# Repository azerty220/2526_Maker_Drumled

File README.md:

# 2526_Maker_Drumled

## Elise Firmin

### Description :
 
Le projet consiste à mettre des leds sur la caisse-claire d’une batterie. Ces led s’allumeraient lorsque la caisse-claire reçoit un coup. De plus, il y aurait un encodeur permettant de choisir la couleur de l’éclairage.
Le projet a pour but d’être amovible ; c’est-à-dire qu’il puisse être ajouté puis retiré de la caisse claire. 
Une partie conception 3D est envisagée afin de mettre le projet sur le contour de la caisse claire sans gêner les frappes du batteur, et qu’il n’y ait pas besoin de démonter les peaux pour insérer les leds. Ainsi, nous évitons de faire des trous dans une caisse claire afin de relier l’encodeur.

### Quelques images d'une caisse claire et de ce que l'on trouve actuellement sur le marché :

#### Exemple de caisse claire :
Nous pouvons voir le fût sur lequel l'on pourra fixer le système et le déclencheur que l'on ne doit pas gêner en revanche. 

#### Système d'éclairage existant :

#####

#####

### Rétroplanning du projet :

Se référer à la partie "Projects" avec le nom "Retroplanning".

## Mécanique :

Il a fallu faire attention que le timbre puisse s'enclencher et se déclencher sans problème. Aussi, ne pas supperposer la partie mécanique aux pièces mécaniques de la caisse-claire elle-même. L'imprimante 3D a été choisie de façon à qu'elle ait un plateau suffisamment grand pour imprimer cette pièce mécanique. 

La partie mécanique se fait en 3 parties :

- 2 parties pour l'anneau autour de la caisse claire, qui s'aimante afin que le tout tienne autour de la caisse-claire. Les aimants sont choisis assez puissants (12kg minimum conseillé), et le tout est assez solide pour ne pas glisser vers le bas. L'une des moitiés d'anneau est adaptée pour recevoir le pcb qui se fixe à l'aide de vis et d'un fer à souder chaud. 

- Le support de la batterie, qui possède 4 trous afin de pouvoir le fixer à l'anneau autour de la caisse claire, à l'aide de vis et d'un fer à soudé chaud.

## Le code :

Le seuil du capteur est à régler dans le code du projet. Le code est séparé en plusieurs parties avec notamment les fonctions importantes qui sont exécutées dans la boucle du main. Un fichier concerne l'acquisition du capteur, un autre les données envoyées à la bande neopixel selon la couleur dirigée par le bouton hardware, et l'acquisition du capteur. 

## La batterie :

Malheureusement, la batterie construite ne permet pas de gérer les appels de courants du circuit, en revanche, en branche une alimentation électrique, le projet est fonctionnel. Il faut changer le composant qui permet de rguler les batteries qui sont en série pour en prendre un plus performant, ou bien utiliser une batterie qui possède une seule cellule est une autre soluton. 

## Le hardware

Plusieurs connectiques de composants ont été adaptées pour avoir des connectiques plus petites et réduire la taille du pcb. Notamment la connectique du ruban de led neopixels pour la convertir en un connecteur jmc de petite taille. 

De plus, lors des tests du projet, le maintien du bouton reset était nécessaire pour la compilatiion du code ; ainsi, la résistance R3 du pcb est inutile : elle s'enlève très facilement du pcb à l'aide d'un coupe-ongle par exemple. Ou bien, sans fer à souder, la température d'un briquet étant de 800°C à 1000°C, cela peut être tenté ; mais attention au risque de brûlure. 

La petite taille du pcb permet un poids léger. 

Le PCB a été conçu à l'aide du logiciel KiCad.

## Piste d'amélioration du projet :

Le projet pourrait être amélioré grâce à des effets codés comme un chazer par exmple, puis un bouton hardware associé. 
De plus, il pourrait être pertinent de mettre un bouton qui permettrait en appuyant 4 fois dessus par l'utilisateur de déterminer un BPM et que les led ne s'allument plus à chaque coup cette fois ci, mais à chaque temps, ce qui constiturait une aide pour le batteur pour conserver le tempo.
En mêlant cette dernière idée avec le projet initial, et étendu à la batterie tout entière, cela donnerait l'accès à des personnes mal entendante à cet instrument, que ce soit une sourdité partiel ou complète.

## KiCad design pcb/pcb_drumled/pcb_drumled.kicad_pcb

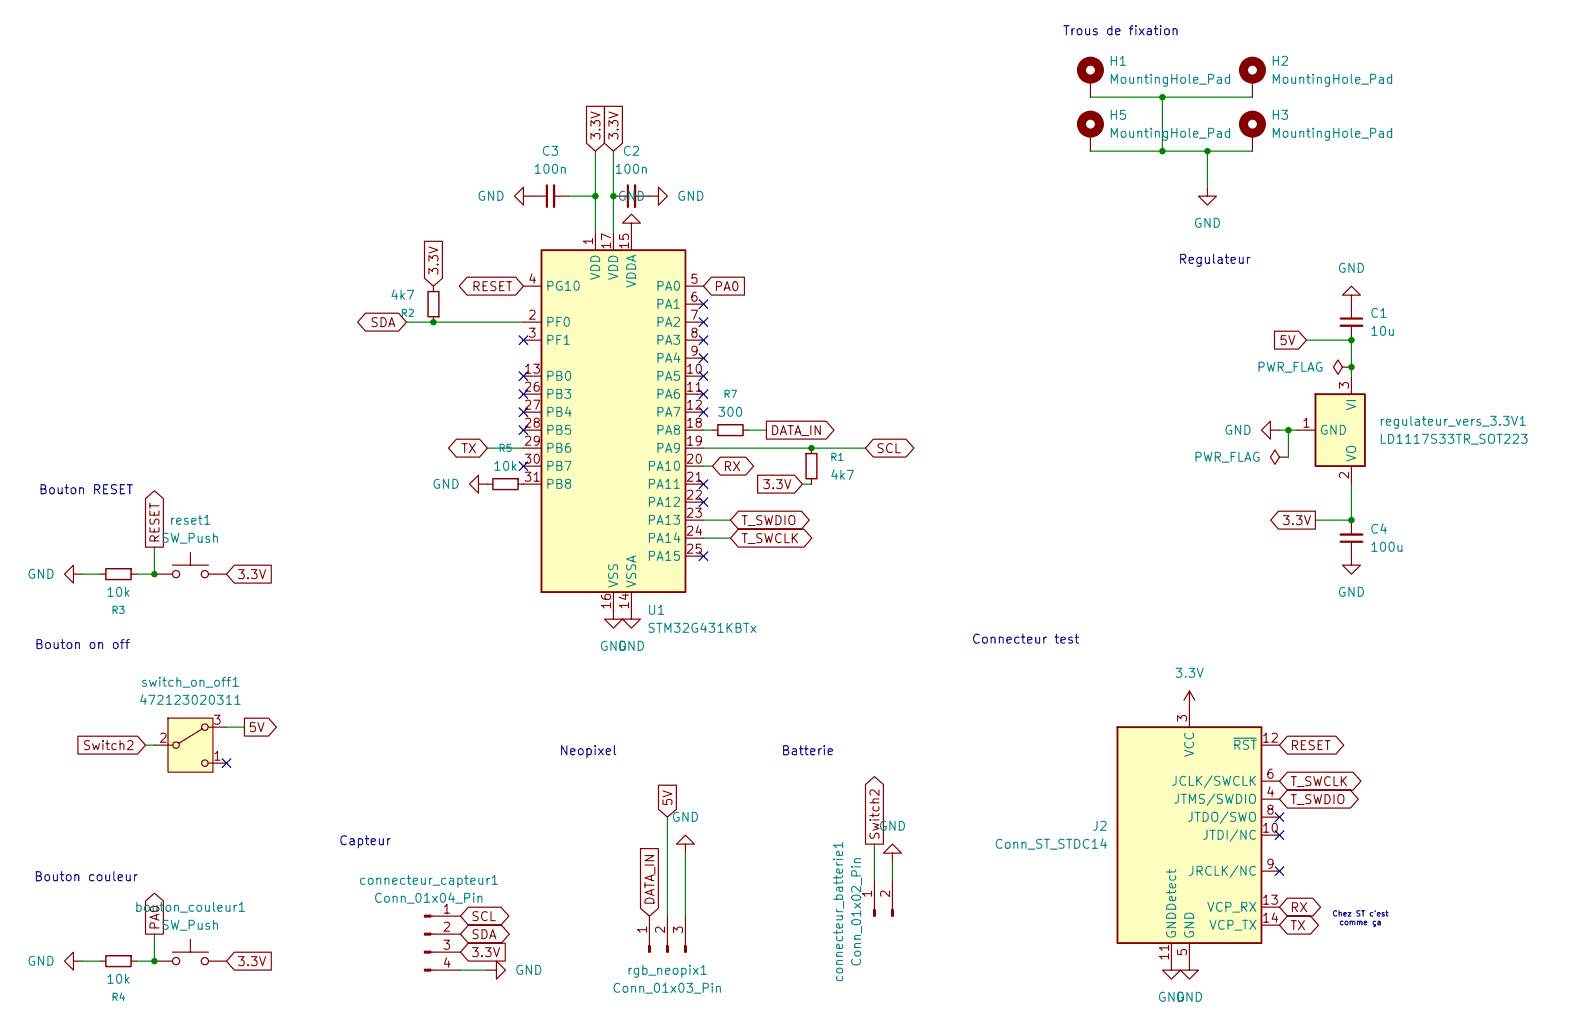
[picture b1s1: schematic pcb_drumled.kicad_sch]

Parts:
C1: 10u; C_0603_1608Metric
C2, C3: 100n; C_0603_1608Metric
C4: 100u; C_0603_1608Metric
H1, H2, H3, H5: MountingHole_Pad; MountingHole_2.2mm_M2_Pad
J2: Conn_ST_STDC14; PinHeader_2x07_P1.27mm_Vertical_SMD
R1, R2: 4k7; R_0603_1608Metric
R3, R4, R5: 10k; R_0603_1608Metric
R7: 300; R_0603_1608Metric
U1: STM32G431KBTx; LQFP-32_7x7mm_P0.8mm
bouton_couleur1: SW_Push; button
connecteur_batterie1: Conn_01x02_Pin; JST_EH_B2B-EH-A_1x02_P2.50mm_Vertical
connecteur_capteur1: Conn_01x04_Pin; PinHeader_1x04_P1.00mm_Vertical
regulateur_vers_3.3V1: LD1117S33TR_SOT223; SOT-223-3_TabPin2
reset1: SW_Push; button
rgb_neopix1: Conn_01x03_Pin; JST_EH_S3B-EH_1x03_P2.50mm_Horizontal
switch_on_off1: 472123020311

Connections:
3.3V: C2.1, C3.2, C4.2, J2.3 (VCC), R1.2, R2.2, U1.1 (VDD), U1.17 (VDD), bouton_couleur1.2, connecteur_capteur1.3, regulateur_vers_3.3V1.2 (VO), reset1.2
5V: C1.2, regulateur_vers_3.3V1.3 (VI), rgb_neopix1.2, switch_on_off1.3 (A)
DATA_IN: R7.2, rgb_neopix1.1
GND: C1.1, C2.2, C3.1, C4.1, H1.1, H2.1, H3.1, H5.1, J2.5 (GND), J2.7 (GND), J2.11 (GNDDetect), R3.2, R4.2, R5.2, U1.14 (VSSA), U1.15 (VDDA), U1.16 (VSS), U1.32 (VSS), connecteur_batterie1.2, connecteur_capteur1.4, regulateur_vers_3.3V1.1 (GND), rgb_neopix1.3
unnamed: R7.1, U1.18 (PA8)
unnamed: R5.1, U1.31 (PB8)
PA0: R4.1, U1.5 (PA0), bouton_couleur1.1
RESET: J2.12 (~RST), R3.1, U1.4 (PG10), reset1.1
RX: J2.13 (VCP_RX), U1.20 (PA10)
SCL: R1.1, U1.19 (PA9), connecteur_capteur1.1
SDA: R2.1, U1.2 (PF0), connecteur_capteur1.2
Switch2: connecteur_batterie1.1, switch_on_off1.2 (B)
TX: J2.14 (VCP_TX), U1.29 (PB6)
T_SWCLK: J2.6 (JCLK/SWCLK), U1.24 (PA14)
T_SWDIO: J2.4 (JTMS/SWDIO), U1.23 (PA13)

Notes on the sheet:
Chez ST c'est comme ça
Capteur
Trous de fixation
Bouton couleur
Connecteur test
Bouton RESET
Batterie
Bouton on off
Neopixel
Regulateur

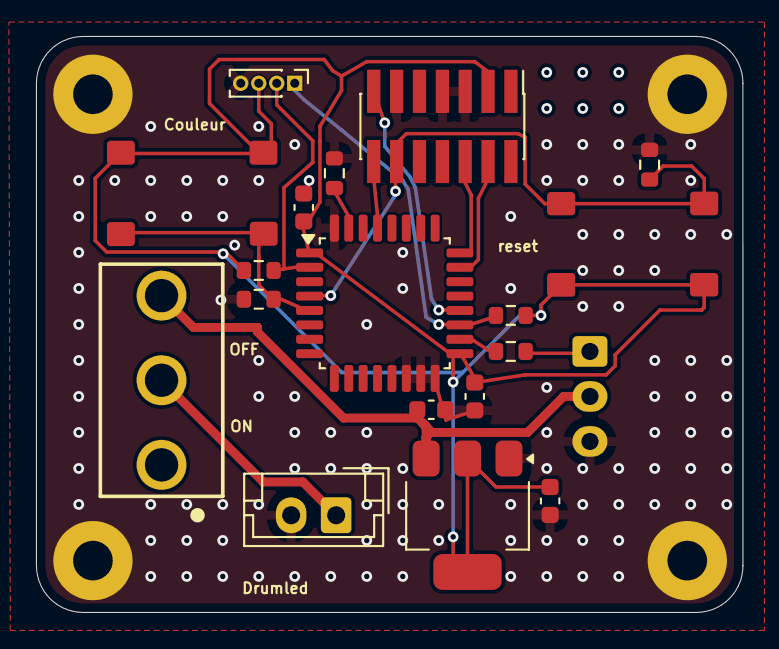
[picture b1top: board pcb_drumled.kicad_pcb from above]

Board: 2 copper layers, 39.3 x 32.0 mm, 23 parts (0 on the bottom side), 15 nets.

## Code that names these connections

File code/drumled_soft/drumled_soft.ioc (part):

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Mcu.Name=STM32G431K(6-8-B)Tx
Mcu.Package=LQFP32
Mcu.UserName=STM32G431KBTx
PA0.GPIOParameters=GPIO_Label
PA0.GPIO_Label=bouton_couleur
PA0.Signal=GPIO_Input
PA10.GPIOParameters=GPIO_Label
PA10.GPIO_Label=rx_test
PA10.Mode=Asynchronous
PA10.Signal=USART1_RX
PA13.Mode=Serial_Wire
PA13.Signal=SYS_JTMS-SWDIO
PA14.Mode=Serial_Wire
PA14.Signal=SYS_JTCK-SWCLK
PA8.GPIOParameters=GPIO_Label
PA8.GPIO_Label=tim_neo
PA8.Signal=S_TIM1_CH1
PA9.GPIOParameters=GPIO_Label
PA9.GPIO_Label=scl_capteur
PA9.Mode=I2C
PA9.Signal=I2C2_SCL
PB6.GPIOParameters=GPIO_Label
PB6.GPIO_Label=tx_test
PB6.Mode=Asynchronous
PB6.Signal=USART1_TX
PF0-OSC_IN.GPIOParameters=GPIO_Label
PF0-OSC_IN.GPIO_Label=sda_capteur
PF0-OSC_IN.Mode=I2C
PF0-OSC_IN.Signal=I2C2_SDA
RCC.HSE_VALUE=8000000
RCC.SYSCLKFreq_VALUE=16000000
board=custom

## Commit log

2026-01-18 ajout_description
2026-01-18 images
2026-01-19 retroplanning
2026-01-19 ajout_nom
2026-01-22 impression3D
2026-01-22 inserts_pla
2026-01-22 reglage impression 3D
2026-01-26 laser
2026-02-02 encore_update
2026-02-02 majpcb
2026-02-16 et encore
2026-03-15 cao_v1
2026-03-15 conception_3d
2026-03-16 pcb_ouiiiiii
2026-03-23 pcb_fini
2026-03-30 gerber
2026-04-01 meca_finie
2026-04-03 je sais plus
2026-04-13 rangement
2026-04-13 photo et video
2026-04-13 code
2026-04-20 code en cours
2026-04-22 code_new
2026-04-22 on/off_pcb
2026-05-02 debug
2026-05-03 video et rendus tp
2026-05-03 Expand README with project details and improvements
    Added detailed sections on mechanics, code, battery, hardware, and potential improvements for the project.
